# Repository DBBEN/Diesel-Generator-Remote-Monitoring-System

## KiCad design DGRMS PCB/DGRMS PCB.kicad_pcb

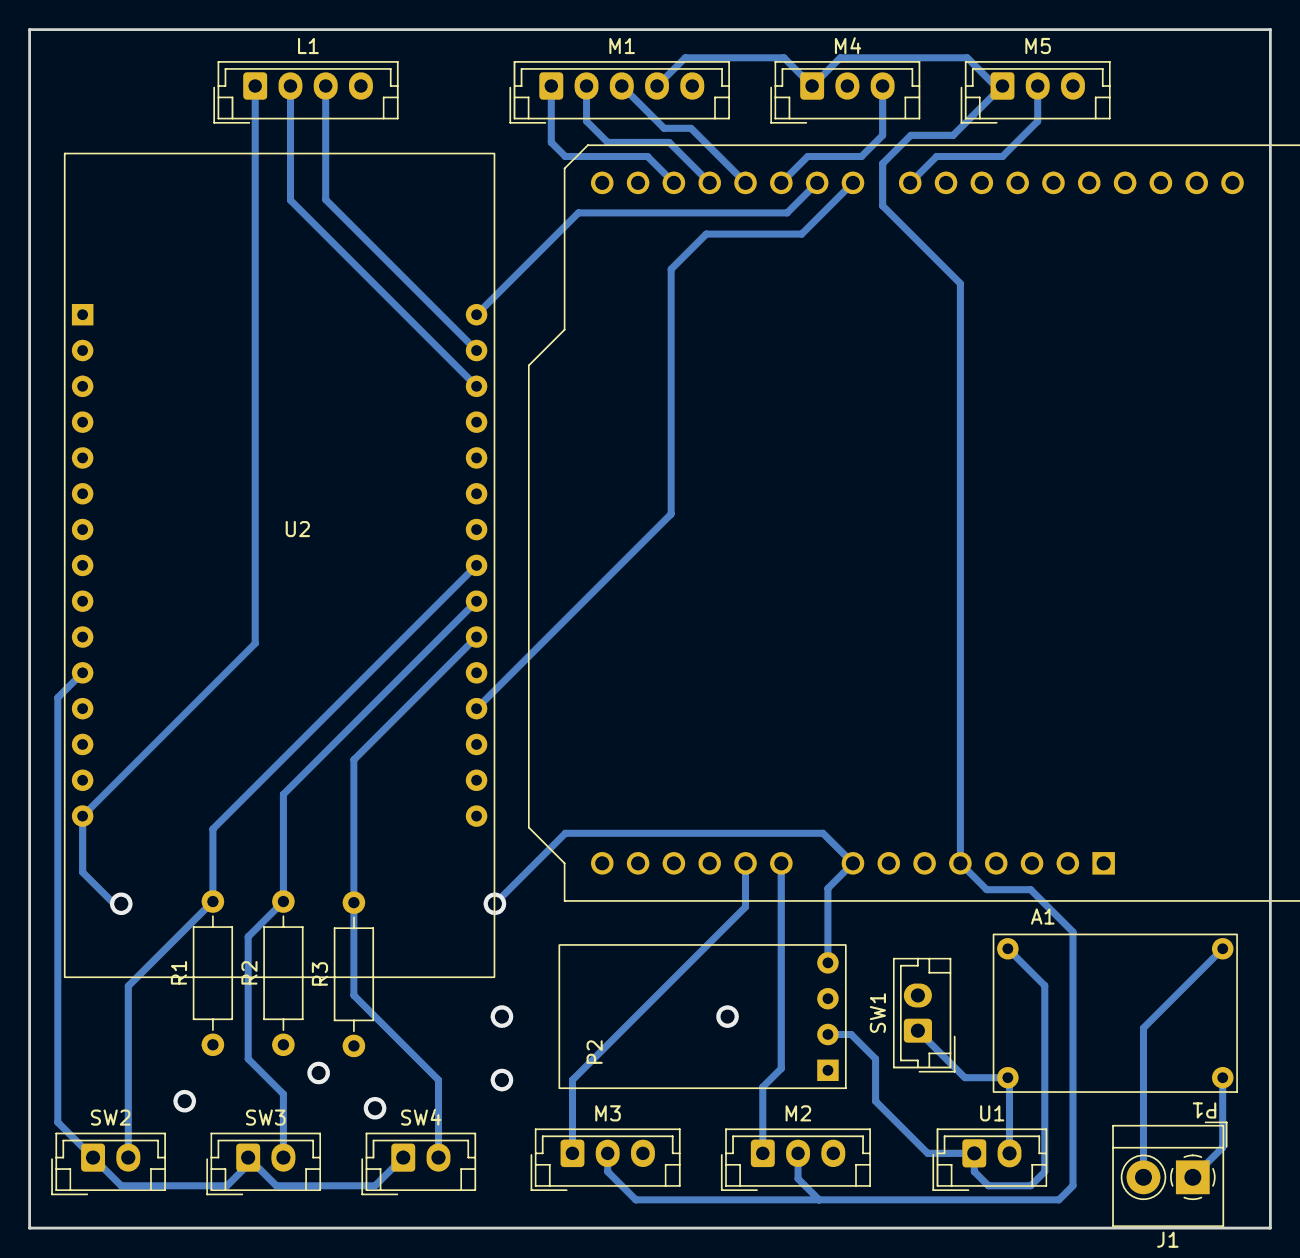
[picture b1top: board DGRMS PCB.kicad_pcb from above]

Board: 2 copper layers, 88.0 x 85.0 mm, 19 parts (0 on the bottom side), 22 nets.

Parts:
A1: UNO; Arduino_UNO_R3
J1: PWR IN; TerminalBlock_4Ucon_1x02_P3.50mm_Horizontal
L1: LCD DISPLAY; JST_EH_B4B-EH-A_1x04_P2.50mm_Vertical
M1: THERMOCOUPLE; JST_EH_B5B-EH-A_1x05_P2.50mm_Vertical
M2, M3: PIEZO; JST_EH_B3B-EH-A_1x03_P2.50mm_Vertical
M4: INFRARED; JST_EH_B3B-EH-A_1x03_P2.50mm_Vertical
M5: 220V DETECT; JST_EH_B3B-EH-A_1x03_P2.50mm_Vertical
P1: STEP DOWN; Mini Step-Down 2
P2: STEP DOWN; Mini Step-Down
R1, R2, R3: 1K; R_Axial_DIN0207_L6.3mm_D2.5mm_P10.16mm_Horizontal
SW1: PWR SW; JST_EH_B2B-EH-A_1x02_P2.50mm_Vertical
SW2, SW3, SW4: SW_Push; JST_EH_B2B-EH-A_1x02_P2.50mm_Vertical
U1: 2S_BMS; JST_EH_B2B-EH-A_1x02_P2.50mm_Vertical
U2: WiFi; NodeMCU V3

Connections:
+3V3: SW2.1, SW3.1, SW4.1, U2.11 (3.3V)
+5VP: A1.5 (+5V), M1.4 (VCC), M2.2 (VCC), M3.2 (VCC), M4.1 (VCC), M5.1 (VCC)
BUTTON_1: R1.2, SW2.2, U2.23 (D5(GPIO14))
BUTTON_2: R2.2, SW3.2, U2.22 (D6(GPIO12))
BUTTON_3: R3.2, SW4.2, U2.21 (D7(GPIO13))
GND: A1.6 (GND), A1.7 (GND), A1.29 (GND), L1.4 (GND), M1.5 (GND), M2.3 (GND), M3.3 (GND), M4.2 (GND), M5.3 (GND), P2.3 (GND), R1.1, R2.1, R3.1, SW1.2 (B), U2.10 (GND), U2.17 (GND), U2.24 (GND)
I2C_SCL: L1.3 (SCL), U2.29 (D1(GPIO5))
I2C_SDA: L1.2 (SDA), U2.28 (D2(GPIO4))
IR_OUT: A1.20 (D5), M4.3 (DO)
unnamed: J1.1, P1.2 (IN-)
unnamed: J1.2, P1.1 (IN+)
unnamed: P1.3 (OUT+), P2.2 (IN+), U1.1 (+)
unnamed: P1.4 (OUT-), SW1.1 (A), U1.2 (-)
PIEZO1_OUT: A1.9 (A0), M2.1 (S)
PIEZO2_OUT: A1.10 (A1), M3.1 (S)
TC_CS: A1.18 (D3), M1.2 (CS)
TC_SCK: A1.19 (D4), M1.3 (SCK)
TC_SO: A1.17 (D2), M1.1 (SO)
VCC: A1.8 (VIN), L1.1 (VCC), P2.4 (VO+), U2.15 (VIN)
V_DETECT: A1.23 (D8), M5.2 (OUT)
WIFI_STATUS_PIN: A1.21 (D6), U2.30 (D0(GPIO16))
WIFI_TX: A1.22 (D7), U2.19 (RX(DPIO3))

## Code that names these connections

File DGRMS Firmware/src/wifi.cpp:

#include <Arduino.h>
#include <ESP8266WiFi.h>
#include <Firebase_ESP_Client.h>
#include <DNSServer.h>
#include <ESP8266WebServer.h>
#include <WiFiManager.h>
#include <ArduinoJson.h>
#include <NTPClient.h>
#include <WiFiUdp.h>
#include <LiquidCrystal_I2C.h>

#include "addons/TokenHelper.h"
#include "addons/RTDBHelper.h"

//  PINOUTS ==================================
#define WIFI_READY_PIN                D0
#define I2C_SDA                       D2 
#define I2C_SCL                       D1
#define BUTTON_1                      D5
#define BUTTON_2                      D6
#define BUTTON_3                      D7

#define LCD_COLUMNS                   16
#define LCD_ROWS                      4
#define LCD_I2C_ADDR                  0x27
// ===========================================

#define API_KEY         "AIzaSyAvwcewC-_jeyFp00PjPWkHoer1C9FyoHM"
#define DATABASE_URL    "https://diesel-generator-monitoring-default-rtdb.asia-southeast1.firebasedatabase.app/"
#define PROJECT_ID      "diesel-generator-monitoring"

// Define NTP Client to get time
WiFiUDP ntpUDP;
NTPClient timeClient(ntpUDP, "pool.ntp.org");

// Variable to save current epoch time
int timestamp;

FirebaseData fbdo;
FirebaseAuth auth;
FirebaseConfig config;
LiquidCrystal_I2C lcd(LCD_I2C_ADDR, LCD_COLUMNS, LCD_ROWS);

int rpm, powerStatus, temperature, harmo, voltage;
float current;
int button1State, button2State, button3State;
int displaySelect = 1;
unsigned long sendDataPrevMillis, prevTime = 0;
bool signupOK, messageReady = false;
char displayBuff[20];
String msg;

// Function that gets current epoch time
unsigned long getTime() {
  timeClient.update();
  unsigned long now = timeClient.getEpochTime();
  return now;
}

void setup(){
  Serial.begin(9600);
  timeClient.begin();
  lcd.init();
  lcd.backlight();
  pinMode(WIFI_READY_PIN, OUTPUT);
  pinMode(BUTTON_1, INPUT);
  pinMode(BUTTON_2, INPUT);
  pinMode(BUTTON_3, INPUT);
  digitalWrite(WIFI_READY_PIN, LOW);
  lcd.print("Setting Up...");

  WiFiManager wifiManager;
  wifiManager.autoConnect("Generator Monitoring System");

  config.api_key = API_KEY;
  config.database_url = DATABASE_URL;

  /* Sign up */
  if (Firebase.signUp(&config, &auth, "", "")){
    Serial.println("ok");
    signupOK = true;
  }
  else{
    Serial.printf("%s\n", config.signer.signupError.message.c_str());
  }

  config.token_status_callback = tokenStatusCallback; 
  
  Firebase.begin(&config, &auth);
  Firebase.reconnectWiFi(true);

  digitalWrite(WIFI_READY_PIN, HIGH);
  lcd.clear();
  lcd.print("Ready");
  delay(2000);
  lcd.clear();
}

void loop(){
  if(Serial.available() > 0){
    StaticJsonDocument<500> doc;
    DeserializationError err = deserializeJson(doc, Serial);
    if (err == DeserializationError::Ok) {
      temperature = doc["temp"].as<int>();
      rpm = doc["rpm"].as<int>();
      harmo = doc["harmo"].as<int>();
      powerStatus = doc["ps"].as<int>();
      voltage = doc["vol"].as<int>();
      current = doc["cur"].as<float>();
    } 
    else {
      while (Serial.available() > 0) Serial.read();
    }
    messageReady = true;
  }

  if(messageReady){
    lcd.clear();

    switch (displaySelect)
    {
      case 1:
        //display temp
        lcd.setCursor(0, 0);
        lcd.print("TEMPERATURE:");
        lcd.setCursor(0, 1);
        sprintf(displayBuff, "%d%cC", temperature, char(223));
        lcd.print(displayBuff);
        break;
      case 2:
        //display rpm
        lcd.setCursor(0, 0);
        lcd.print("TACHOMETER:");
        lcd.setCursor(0, 1);
        sprintf(displayBuff, "%d RPM", rpm);
        lcd.print(displayBuff);
        break;
      case 3:
        //display harmo
        lcd.setCursor(0, 0);
        lcd.print("HARMONICS:");
        lcd.setCursor(0, 1);
        sprintf(displayBuff, "%d Hz", harmo);
        lcd.print(displayBuff);
        break;
      case 4:
        //display voltage
        lcd.setCursor(0, 0);
        lcd.print("VOLTAGE:");
        lcd.setCursor(0, 1);
        sprintf(displayBuff, "%d V", voltage);
        lcd.print(displayBuff);
        break;
      case 5:
        //display current
        lcd.setCursor(0, 0);
        lcd.print("CURRENT:");
        lcd.setCursor(0, 1);
        sprintf(displayBuff, "%.2f A", current);
        lcd.print(displayBuff);
        break;
    }
  
    if(Firebase.ready() && signupOK && (millis() - sendDataPrevMillis > 1000 || sendDataPrevMillis == 0) && temperature > 0){
      FirebaseJson content;
      timestamp = getTime();
      content.set("/temperature", temperature);
      content.set("/rpm", rpm);
      content.set("/harmo", harmo);
      content.set("/powerStatus", powerStatus);
      content.set("/timestamp/", timestamp);
      content.set("/voltage", voltage);
      content.set("/current", current);

      if(Firebase.RTDB.setJSON(&fbdo, "/generatorReadings", &content)); else Serial.println("FAILED: " + fbdo.errorReason());
      if(Firebase.RTDB.pushJSON(&fbdo, "/readingRecords/", &content)); else Serial.println("FAILED: " + fbdo.errorReason());
    

      sendDataPrevMillis = millis();
    }
    
    messageReady = false;
  }

  if(button1State && !button2State && !button3State){
    displaySelect = 1;
  } else if (!button1State && button2State && !button3State) {
    displaySelect = 2;
  } else if (!button1State && !button2State && button3State) {
    displaySelect = 3;
  } else if (button1State && button2State && !button3State) {
    displaySelect = 4;
  } else if (!button1State && button2State && button3State) {
    displaySelect = 5;
  }

  if(millis() - prevTime >= 100){
    button1State = digitalRead(BUTTON_1); 
    button2State = digitalRead(BUTTON_2); 
    button3State = digitalRead(BUTTON_3);
    prevTime = millis();
  }
}

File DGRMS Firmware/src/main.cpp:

#include <Arduino.h>
#include <max6675.h>
#include <arduinoFFT.h>

//  PINOUTS ==================================
#define PIEZO1_SENSOR           0   //ANALOG
#define VOLTAGE_SENSOR          1   //ANALOG
#define CURRENT_SENSOR          2   //ANALOG
#define THERMOC_DO              2  
#define THERMOC_CS              5
#define THERMOC_CLK             4
#define IR_OUT                  3
#define WIFI_STATUS_PIN         6
#define WIFI_TX                 7
#define VIN_DETECT              8
// ===========================================

#define VOLTAGE_SAMPLES         60
#define CURR_M                  0.0002155405
#define CURR_B                  0
#define VOL_M                   0.855596
#define VOL_B                   -2.566787

#define SAMPLES                 128
#define SAMPLING_FREQ           5000

#define RPM_MAX                 1800
#define RPM_MIN                 0

int currTemp, rpm, calReading, piezoCalibration, voltage;
float current;
unsigned int period, detect_ctr = 0;
int _random = 0;
int powerStatus;
int buttonStateFalling, lastButtonStateFalling = 1;
unsigned long t1, t2, prevMillis, lastTime, now;
volatile unsigned long pulseCount = 0;
bool detectFlag, rpmFlag, harmoFlag = false;

double vReal[SAMPLES];
double vImag[SAMPLES];
int previous_rpm = 0;
unsigned int harmo, sampling_period_us;
unsigned long microseconds;

MAX6675 tempSense(THERMOC_CLK, THERMOC_CS, THERMOC_DO);
arduinoFFT FFT = arduinoFFT();

int findFrequency(){
  for(int i = 0; i < SAMPLES; i++){
    microseconds = micros();    
    vReal[i] = analogRead(PIEZO1_SENSOR);
    vImag[i] = 0;
    while(micros() < (microseconds + sampling_period_us));
  }
 
  FFT.Windowing(vReal, SAMPLES, FFT_WIN_TYP_HAMMING, FFT_FORWARD);
  FFT.Compute(vReal, vImag, SAMPLES, FFT_FORWARD);
  FFT.ComplexToMagnitude(vReal, vImag, SAMPLES);
  double peak = FFT.MajorPeak(vReal, SAMPLES, SAMPLING_FREQ);

  peak = peak * 0.97;
  return round(peak);
}

int getVoltage(){
  int volrms, analogReading;
  int highest, lowest;
  
  volrms = 0;
  highest = 509;
  lowest = 509;

  for(int j = 0; j < VOLTAGE_SAMPLES; j++){
    analogReading = analogRead(VOLTAGE_SENSOR);
    if(analogReading > highest) highest = analogReading;
    else if(analogReading < lowest) lowest = analogReading;
    delay(15);
  }

  volrms = highest - lowest;
  volrms = (volrms * VOL_M) + VOL_B;

  if(volrms <= 3) volrms = 0;

  return volrms;
}

float getCurrent(){
  int x = analogRead(CURRENT_SENSOR);
  return ((CURR_M * x) + CURR_B);
}

void sendtoWiFi(){
  Serial.print("{\"temp\":");
  Serial.print(currTemp);
  Serial.print(",\"rpm\":");
  Serial.print(rpm);
  Serial.print(",\"harmo\":");
  Serial.print(harmo);
  Serial.print(",\"ps\":");
  Serial.print(powerStatus);
  Serial.print(",\"vol\":");
  Serial.print(voltage);
  Serial.print(",\"cur\":");
  Serial.print(current, 2);
  Serial.print("}");
}

void countPulse(){
  pulseCount++;
}

void setup() {
  sampling_period_us = round(1000000 * (1.0 / SAMPLING_FREQ));
  Serial.begin(9600);
  pinMode(WIFI_STATUS_PIN, INPUT);
  pinMode(VIN_DETECT, INPUT);
  pinMode(IR_OUT, INPUT);
  delay(100);
  while(!digitalRead(WIFI_STATUS_PIN));
  attachInterrupt(digitalPinToInterrupt(IR_OUT), countPulse, FALLING);
}

void loop() {
  //harmonics
  harmo = findFrequency();

  now = millis();
  if(now - lastTime > 1000){
    //tachometer
    detachInterrupt(digitalPinToInterrupt(IR_OUT));
    rpm = (pulseCount * 60000) / (now - lastTime);
    if(rpm >= RPM_MAX) rpm = RPM_MAX + _random;
    if (rpm <= 0) {
      _random = random(1, 100);
      rpm = RPM_MIN;
    }
    
    pulseCount = 0;
    lastTime = millis();
    attachInterrupt(digitalPinToInterrupt(IR_OUT), countPulse, FALLING);

    //thermocouple
    currTemp = (int)tempSense.readCelsius();

    //power status
    if(digitalRead(VIN_DETECT) == LOW) powerStatus = 1;
    else powerStatus = 0;

    //voltage
    voltage = getVoltage();

    //current
    current = getCurrent();
    
    sendtoWiFi();
  }

}

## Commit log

2023-11-10 Added files for website
